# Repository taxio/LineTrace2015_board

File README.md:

# LineTrace2015_Board

## Specification

|Microcomputer|STM32F405RGT6|
|:--:|:--:|
|MotorDriver|TB6612FNG|
|LED|HIRL8810|
|Photoreflector|ST-1KLA|

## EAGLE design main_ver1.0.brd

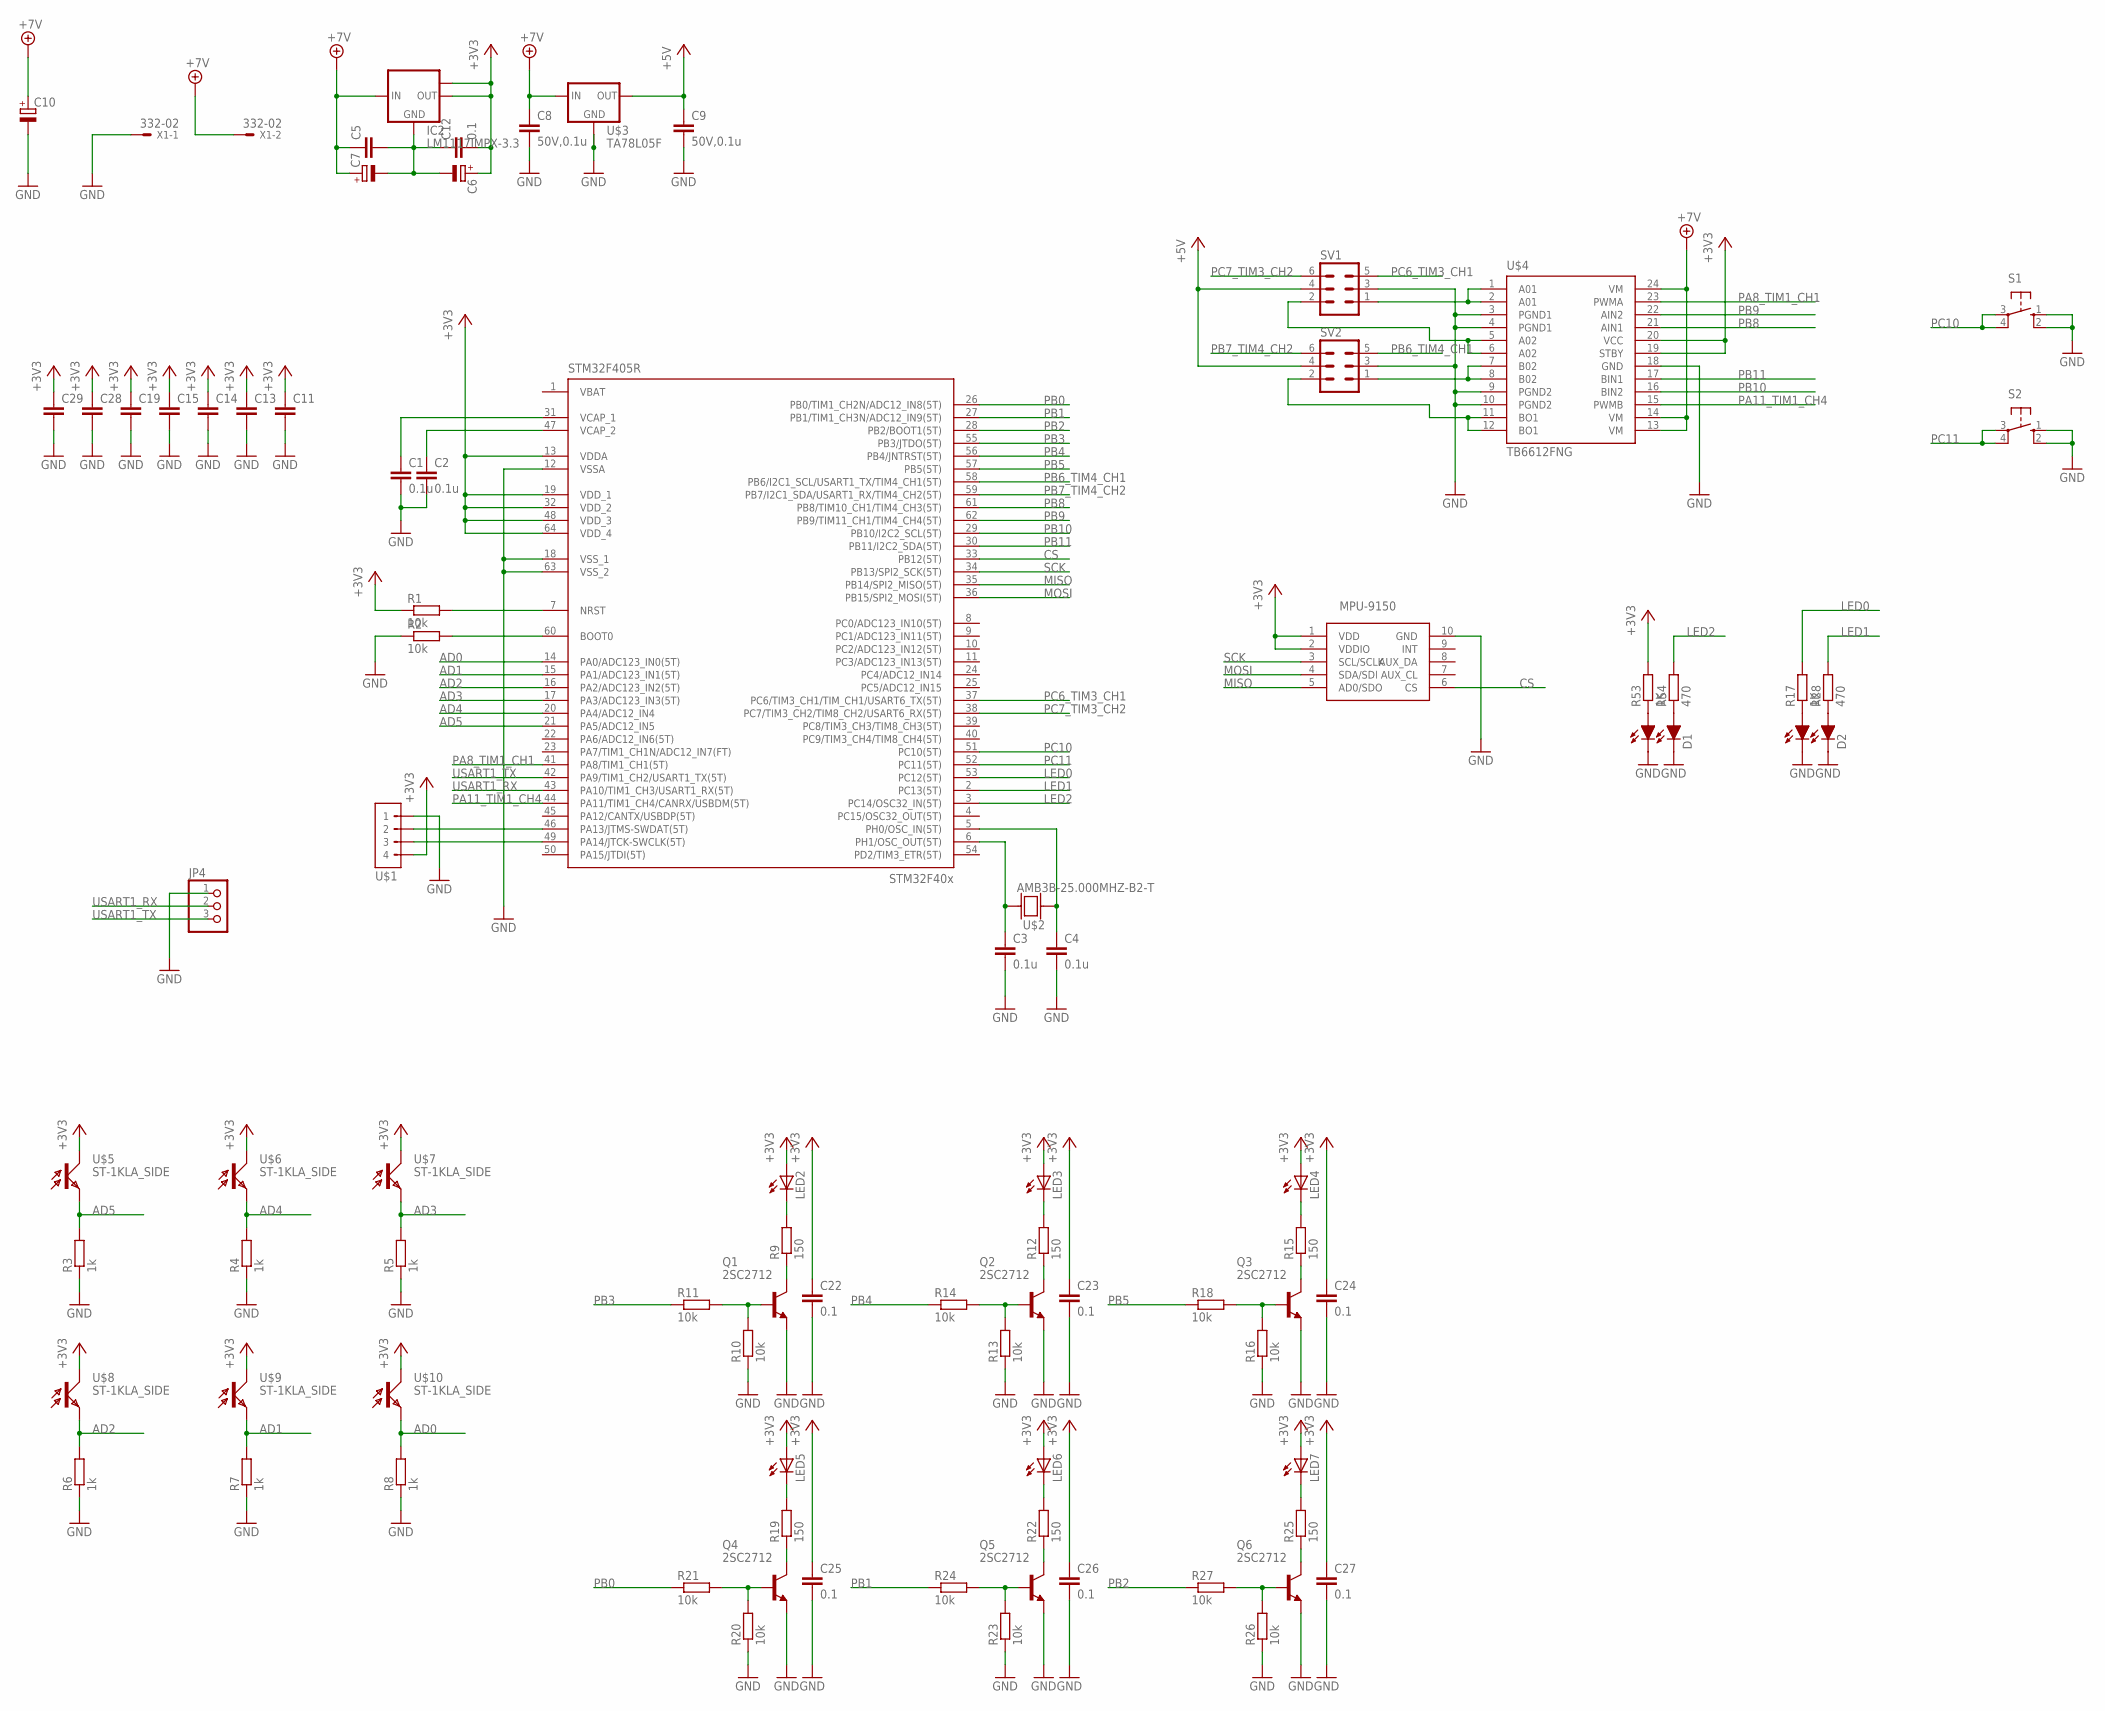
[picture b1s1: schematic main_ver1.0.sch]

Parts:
C1, C2, C3, C4: 0.1u; C0603K
C5: C-EUC0603; C0603
C6, C7, C10: CPOL-EUSANYO_SMD_A5; SANYO-OSCON_SMD_A5
C8, C9: 50V,0.1u; C0603K
C11, C13, C14, C15, C19, C28, C29: C-EUC0603K; C0603K
C12, C22, C23, C24, C25, C26, C27: 0.1; C0603
D1, D2: SEC2XX4; LED3025
IC2: LM1117IMPX-3.3; SOT223
JP4: PINHD-1X3/90; 1X03/90
LED2, LED3, LED4, LED5, LED6, LED7: LEDSFH480; SFH480
MPU-9250: MPU-9250
Q1, Q2, Q3, Q4, Q5, Q6: 2SC2712; SC-59(TYPE1)
R1, R2, R10, R11, R13, R14, R16, R18, R20, R21, R23, R24, R26, R27: 10k; R0603
R3, R4, R5, R6, R7, R8: 1k; R0603
R9, R12, R15, R19, R22, R25: 150; R0603
R17, R53: 1K; R0603
R28, R54: 470; R0603
S1, S2: 10-XX; B3F-10XX
STM32F405R: STM32F405R; TQFP64
SV1, SV2: ML6
U$1: TOP_TYPE_4PIN
U$2: AMB3B-25.000MHZ-B2-T; 4LCC
U$3: TA78L05F; SOT89
U$4: TB6612FNG; SSOP24
U$5, U$6, U$7, U$8, U$9, U$10: ST-1KLA_SIDE; TO18-SIDE
X1: 332-02

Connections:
+3V3: C6.+, C11.1, C12.2, C13.1, C14.1, C15.1, C19.1, C22.1, C23.1, C24.1, C25.1, C26.1, C27.1, C28.1, C29.1, IC2.2 (OUT), IC2.TAB (OUT1), LED2.A, LED3.A, LED4.A, LED5.A, LED6.A, LED7.A, MPU-9250.1 (VDD), MPU-9250.2 (VDDIO), R1.1, R53.2, STM32F405R.13 (VDDA), STM32F405R.19 (VDD_1), STM32F405R.32 (VDD_2), STM32F405R.48 (VDD_3), STM32F405R.64 (VDD_4), U$1.4, U$4.19 (STBY), U$4.20 (VCC), U$5.P$2 (C), U$6.P$2 (C), U$7.P$2 (C), U$8.P$2 (C), U$9.P$2 (C), U$10.P$2 (C)
+5V: C9.1, SV1.4, SV2.4, U$3.1 (OUT)
+7V: C5.1, C7.+, C8.1, C10.+, IC2.3 (IN), U$3.3 (IN), U$4.13 (VM), U$4.14 (VM), U$4.24 (VM), X1.2
AD0: R8.2, STM32F405R.14 (PA0/ADC123_IN0(5T)), U$10.P$1 (E)
AD1: R7.2, STM32F405R.15 (PA1/ADC123_IN1(5T)), U$9.P$1 (E)
AD2: R6.2, STM32F405R.16 (PA2/ADC123_IN2(5T)), U$8.P$1 (E)
AD3: R5.2, STM32F405R.17 (PA3/ADC123_IN3(5T)), U$7.P$1 (E)
AD4: R4.2, STM32F405R.20 (PA4/ADC12_IN4), U$6.P$1 (E)
AD5: R3.2, STM32F405R.21 (PA5/ADC12_IN5), U$5.P$1 (E)
CS: MPU-9250.6 (CS), STM32F405R.33 (PB12(5T))
GND: C1.2, C2.2, C3.2, C4.2, C5.2, C6.-, C7.-, C8.2, C9.2, C10.-, C11.2, C12.1, C13.2, C14.2, C15.2, C19.2, C22.2, C23.2, C24.2, C25.2, C26.2, C27.2, C28.2, C29.2, D1.1 (C0), D1.2 (C1), D2.1 (C0), D2.2 (C1), IC2.1 (GND), JP4.1, MPU-9250.10 (GND), Q1.E, Q2.E, Q3.E, Q4.E, Q5.E, Q6.E, R2.1, R3.1, R4.1, R5.1, R6.1, R7.1, R8.1, R10.1, R13.1, R16.1, R20.1, R23.1, R26.1, S1.1 (S), S1.2 (S1), S2.1 (S), S2.2 (S1), STM32F405R.12 (VSSA), STM32F405R.18 (VSS_1), STM32F405R.63 (VSS_2), SV1.3, SV2.3, U$1.1, U$3.2 (GND), U$3.2@1 (GND1), U$4.3 (PGND1), U$4.4 (PGND1), U$4.9 (PGND2), U$4.10 (PGND2), U$4.18 (GND), X1.1
LED0: R17.2, STM32F405R.53 (PC12(5T))
LED1: R28.2, STM32F405R.2 (PC13(5T))
LED2: R54.2, STM32F405R.3 (PC14/OSC32_IN(5T))
MISO: MPU-9250.5 (AD0/SDO), STM32F405R.35 (PB14/SPI2_MISO(5T))
MOSI: MPU-9250.4 (SDA/SDI), STM32F405R.36 (PB15/SPI2_MOSI(5T))
unnamed: R1.2, STM32F405R.7 (NRST)
unnamed: R2.2, STM32F405R.60 (BOOT0)
unnamed: STM32F405R.49 (PA14/JTCK-SWCLK(5T)), U$1.3
unnamed: STM32F405R.46 (PA13/JTMS-SWDAT(5T)), U$1.2
unnamed: C2.1, STM32F405R.47 (VCAP_2)
unnamed: C1.1, STM32F405R.31 (VCAP_1)
unnamed: C4.1, STM32F405R.5 (PH0/OSC_IN(5T)), U$2.1
unnamed: C3.1, STM32F405R.6 (PH1/OSC_OUT(5T)), U$2.3
unnamed: SV2.1, U$4.7 (B02), U$4.8 (B02)
unnamed: SV2.2, U$4.11 (BO1), U$4.12 (BO1)
unnamed: SV1.2, U$4.5 (A02), U$4.6 (A02)
unnamed: SV1.1, U$4.1 (A01), U$4.2 (A01)
unnamed: D1.3 (A1), R53.1
unnamed: D2.3 (A1), R17.1
unnamed: D2.4 (A0), R28.1
unnamed: Q1.C, R9.1
unnamed: LED2.K (C), R9.2
unnamed: Q2.C, R12.1
unnamed: Q2.B, R13.2, R14.2
unnamed: LED3.K (C), R12.2
unnamed: Q3.C, R15.1
unnamed: Q3.B, R16.2, R18.2
unnamed: D1.4 (A0), R54.1
unnamed: LED4.K (C), R15.2
unnamed: Q4.C, R19.1
unnamed: Q4.B, R20.2, R21.2
unnamed: LED5.K (C), R19.2
unnamed: Q5.C, R22.1
unnamed: Q5.B, R23.2, R24.2
unnamed: LED6.K (C), R22.2
unnamed: Q6.C, R25.1
unnamed: Q6.B, R26.2, R27.2
unnamed: LED7.K (C), R25.2
unnamed: Q1.B, R10.2, R11.2
PA8_TIM1_CH1: STM32F405R.41 (PA8/TIM1_CH1(5T)), U$4.23 (PWMA)
PA11_TIM1_CH4: STM32F405R.44 (PA11/TIM1_CH4/CANRX/USBDM(5T)), U$4.15 (PWMB)
PB0: R21.1, STM32F405R.26 (PB0/TIM1_CH2N/ADC12_IN8(5T))
PB1: R24.1, STM32F405R.27 (PB1/TIM1_CH3N/ADC12_IN9(5T))
PB2: R27.1, STM32F405R.28 (PB2/BOOT1(5T))
PB3: R11.1, STM32F405R.55 (PB3/JTDO(5T))
PB4: R14.1, STM32F405R.56 (PB4/JNTRST(5T))
PB5: R18.1, STM32F405R.57 (PB5(5T))
PB6_TIM4_CH1: STM32F405R.58 (PB6/I2C1_SCL/USART1_TX/TIM4_CH1(5T)), SV2.5
PB7_TIM4_CH2: STM32F405R.59 (PB7/I2C1_SDA/USART1_RX/TIM4_CH2(5T)), SV2.6
PB8: STM32F405R.61 (PB8/TIM10_CH1/TIM4_CH3(5T)), U$4.21 (AIN1)
PB9: STM32F405R.62 (PB9/TIM11_CH1/TIM4_CH4(5T)), U$4.22 (AIN2)
PB10: STM32F405R.29 (PB10/I2C2_SCL(5T)), U$4.16 (BIN2)
PB11: STM32F405R.30 (PB11/I2C2_SDA(5T)), U$4.17 (BIN1)
PC6_TIM3_CH1: STM32F405R.37 (PC6/TIM3_CH1/TIM_CH1/USART6_TX(5T)), SV1.5
PC7_TIM3_CH2: STM32F405R.38 (PC7/TIM3_CH2/TIM8_CH2/USART6_RX(5T)), SV1.6
PC10: S1.3, S1.4 (P1), STM32F405R.51 (PC10(5T))
PC11: S2.3, S2.4 (P1), STM32F405R.52 (PC11(5T))
SCK: MPU-9250.3 (SCL/SCLK), STM32F405R.34 (PB13/SPI2_SCK(5T))
USART1_RX: JP4.2, STM32F405R.43 (PA10/TIM1_CH3/USART1_RX(5T))
USART1_TX: JP4.3, STM32F405R.42 (PA9/TIM1_CH2/USART1_TX(5T))

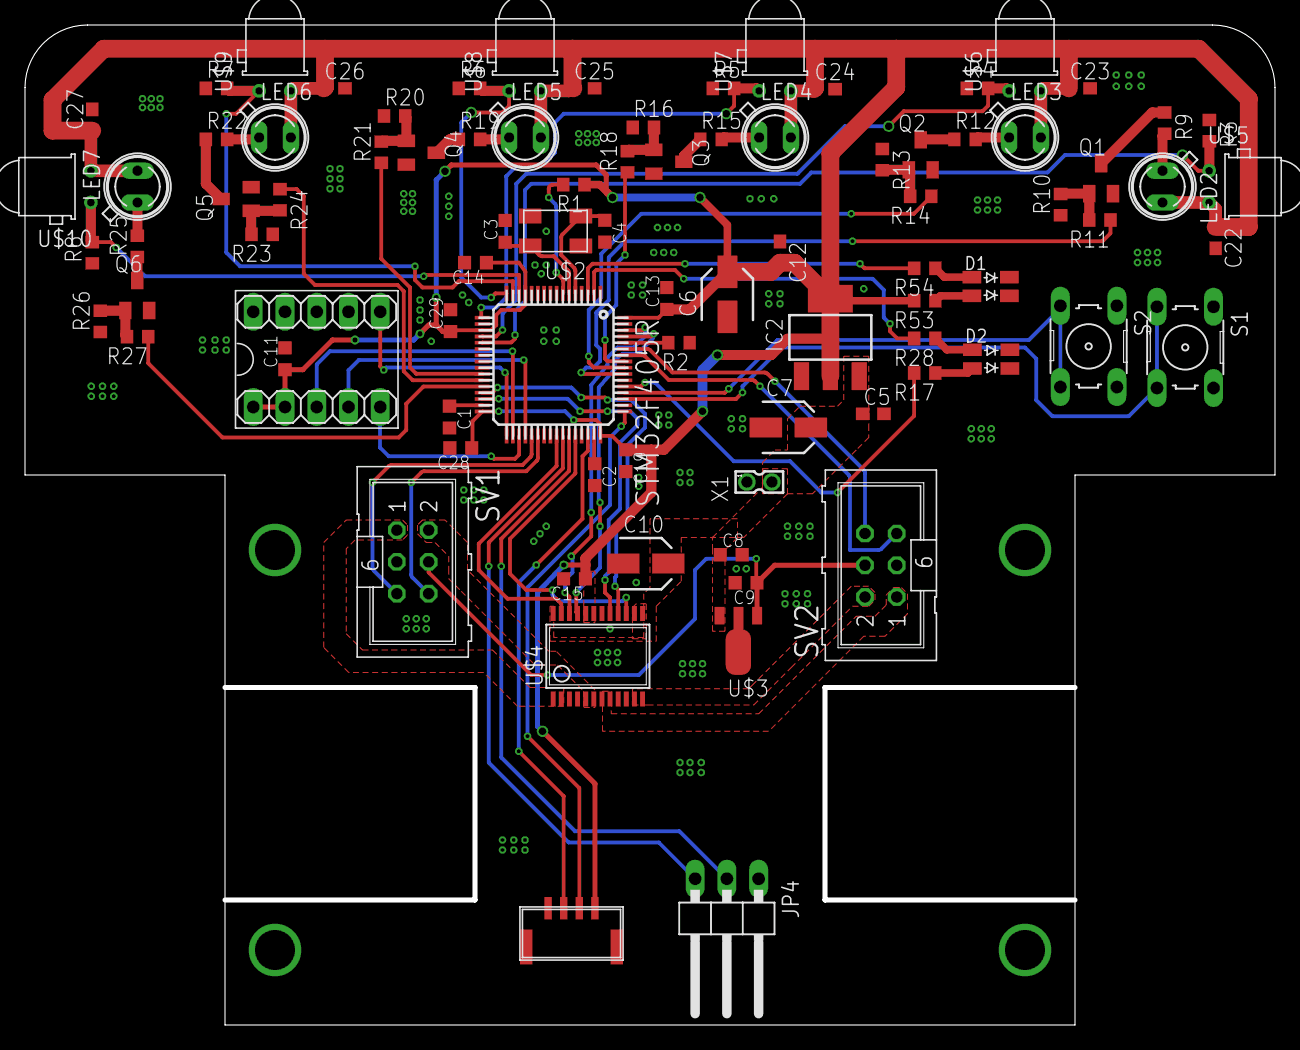
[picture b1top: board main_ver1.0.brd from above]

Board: 2 copper layers, 100.0 x 80.0 mm, 87 parts (0 on the bottom side), 71 nets.

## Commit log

2015-11-11 first
